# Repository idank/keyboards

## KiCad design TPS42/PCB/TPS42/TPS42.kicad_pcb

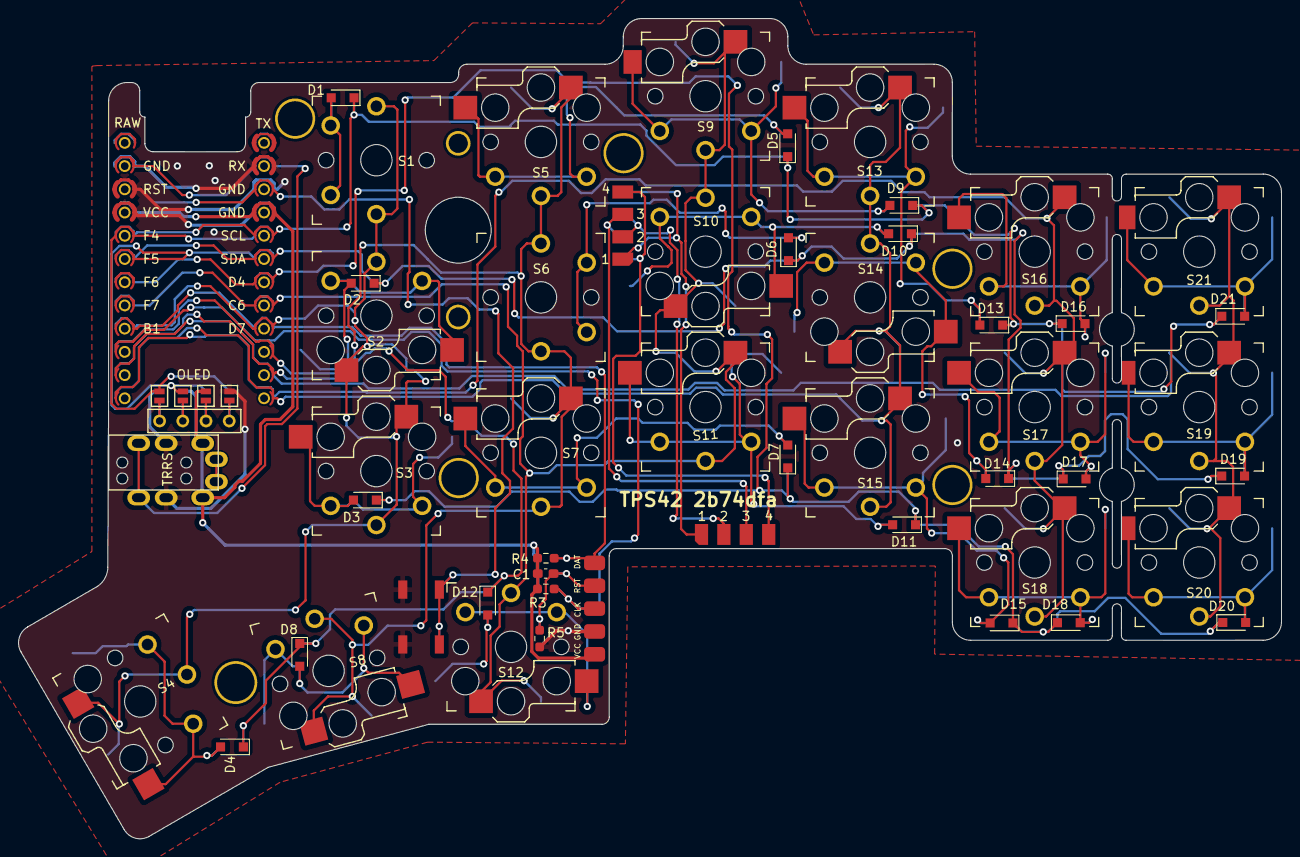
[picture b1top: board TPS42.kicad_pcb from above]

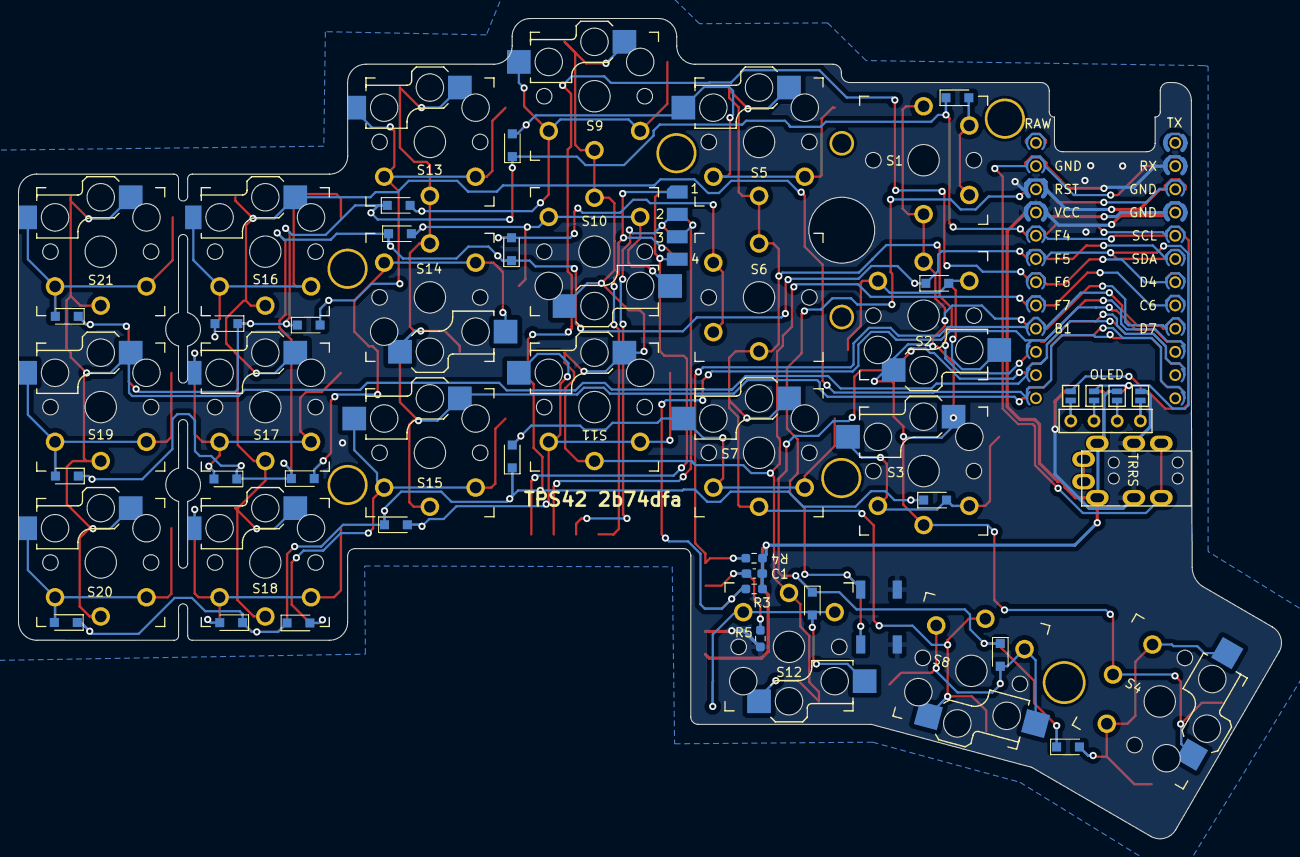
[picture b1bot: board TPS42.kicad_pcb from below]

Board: 2 copper layers, 138.1 x 89.7 mm, 71 parts (7 on the bottom side), 48 nets.

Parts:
C1: 2.2uF; C_0603_1608Metric_Pad1.08x0.95mm_HandSolder_Reversable
D1, D2, D3, D4, D5, D6, D7, D8, D9, D10, D11, D12, D13, D14, D15, D16, D17, D18, D19, D20, D21: D_Small; D_SOD-323_HandSoldering_Reversable
J1: MJ-4PP-9
J2: OLED
J3, J9: TP Sensor Module; TPSensorModule_Connector
J4: TP Module; TPSensorModule_Connector
J7: TrackPoint; TPModule
JP1, JP2, JP3, JP4, JP5, JP6, JP7, JP8: Jumper
R3, R4: 4.7kΩ; R_0603_1608Metric_Pad0.98x0.95mm_HandSolder_Reversable
R5: 100kΩ; R_0603_1608Metric_Pad0.98x0.95mm_HandSolder_Reversable
S1, S6: Switch; SW_PG1350_reversible
S2, S3, S5, S7, S8, S9, S10, S11, S12, S13, S14, S15, S16, S17, S18, S19, S20, S21: Switch; Kailh_socket_PG1350_optional_reversible.kicad_mod
S4: Switch; Kailh_socket_PG1350_125_optional_reversible.kicad_mod
SW2, SW3: Reset; SMD-SW-4_5.1x5.1x2.5
U1: ProMicro; ProMicro_Flipped_v2_A
U4, U5, U7, U8, U9, U12: Hole; HOLE_M2_TH
U11: Hole; TPSensorModule
U14: ProMicro; ProMicro_Flipped_v2_B

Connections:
COL0: S1.1, S2.1, S3.1, S4.1, U1.16 (B1/15), U14.16 (B1/15)
COL1: S5.1, S6.1, S7.1, S8.1, U1.15 (B3/14), U14.15 (B3/14)
COL2: S9.1, S10.1, S11.1, S12.1, U1.17 (F7/A0), U14.17 (F7/A0)
COL3: S13.1, S14.1, S15.1, U1.13 (B6/10), U14.13 (B6/10)
COL4: S16.1, S17.1, S18.1, U1.12 (9/B5), U14.12 (9/B5)
COL5: S19.1, S20.1, S21.1, U1.11 (8/B4), U14.11 (8/B4)
GND: J1.C, J7.4, JP1.1, JP8.1, R5.2, SW2.1, SW3.1, U1.3 (GND), U1.4 (GND), U1.23 (GND), U14.3 (GND), U14.4 (GND), U14.23 (GND)
unnamed: D1.2 (A), S1.2
unnamed: D2.2 (A), S2.2
unnamed: D3.2 (A), S3.2
unnamed: D4.2 (A), S4.2
unnamed: D5.2 (A), S5.2
unnamed: D6.2 (A), S6.2
unnamed: D7.2 (A), S7.2
unnamed: D8.2 (A), S8.2
unnamed: D9.2 (A), S9.2
unnamed: D10.2 (A), S10.2
unnamed: D11.2 (A), S11.2
unnamed: D12.2 (A), S12.2
unnamed: D13.2 (A), S13.2
unnamed: D14.2 (A), S14.2
unnamed: D15.2 (A), S15.2
unnamed: D16.2 (A), S16.2
unnamed: D17.2 (A), S17.2
unnamed: D18.2 (A), S18.2
unnamed: D19.2 (A), S19.2
unnamed: D20.2 (A), S20.2
unnamed: D21.2 (A), S21.2
unnamed: J2.1, JP4.2, JP8.2
unnamed: J2.2, JP3.2, JP7.2
unnamed: J2.3, JP2.2, JP6.2
unnamed: J2.4, JP1.2, JP5.2
unnamed: J3.1, J4.1, J9.1
unnamed: J3.2, J4.2, J9.2
unnamed: J3.3, J4.3, J9.3
unnamed: J3.4, J4.4, J9.4
unnamed: C1.2, J7.2, R5.1
RESET: SW2.2, SW3.2, U1.22 (RST), U14.22 (RST)
ROW0: D1.1 (K), D5.1 (K), D9.1 (K), D13.1 (K), D16.1 (K), D21.1 (K), U1.20 (F4/A3), U14.20 (F4/A3)
ROW1: D2.1 (K), D6.1 (K), D10.1 (K), D14.1 (K), D17.1 (K), D19.1 (K), U1.19 (F5/A2), U14.19 (F5/A2)
ROW2: D3.1 (K), D7.1 (K), D11.1 (K), D15.1 (K), D18.1 (K), D20.1 (K), U1.18 (F6/A1), U14.18 (F6/A1)
ROW3: D4.1 (K), D8.1 (K), D12.1 (K), U1.14 (B2/16), U14.14 (B2/16)
SCL: JP3.1, JP6.1, U1.6 (3/D0/SCL), U14.6 (3/D0/SCL)
SDA: JP4.1, JP5.1, U1.5 (2/D1/SDA), U14.5 (2/D1/SDA)
SERIAL: J1.B, U1.2 (RX1/D2), U14.2 (RX1/D2)
TP_CLK: J7.3, R3.2, U1.10 (7/E6), U14.10 (7/E6)
TP_DATA: J7.1, R4.2, U1.9 (6/D7), U14.9 (6/D7)
VCC: C1.1, J1.D, J7.5, JP2.1, JP7.1, R3.1, R4.1, U1.21 (VCC), U14.21 (VCC)

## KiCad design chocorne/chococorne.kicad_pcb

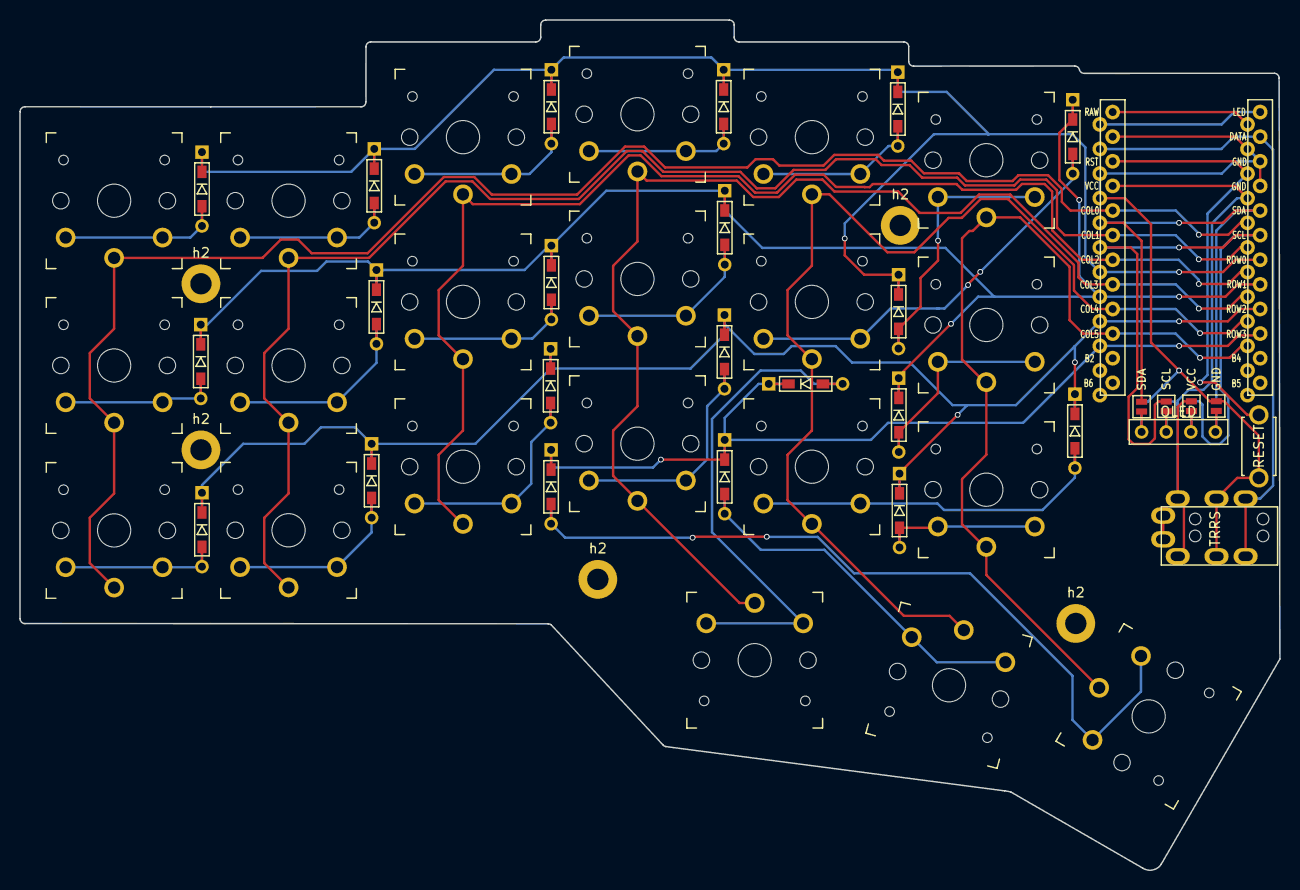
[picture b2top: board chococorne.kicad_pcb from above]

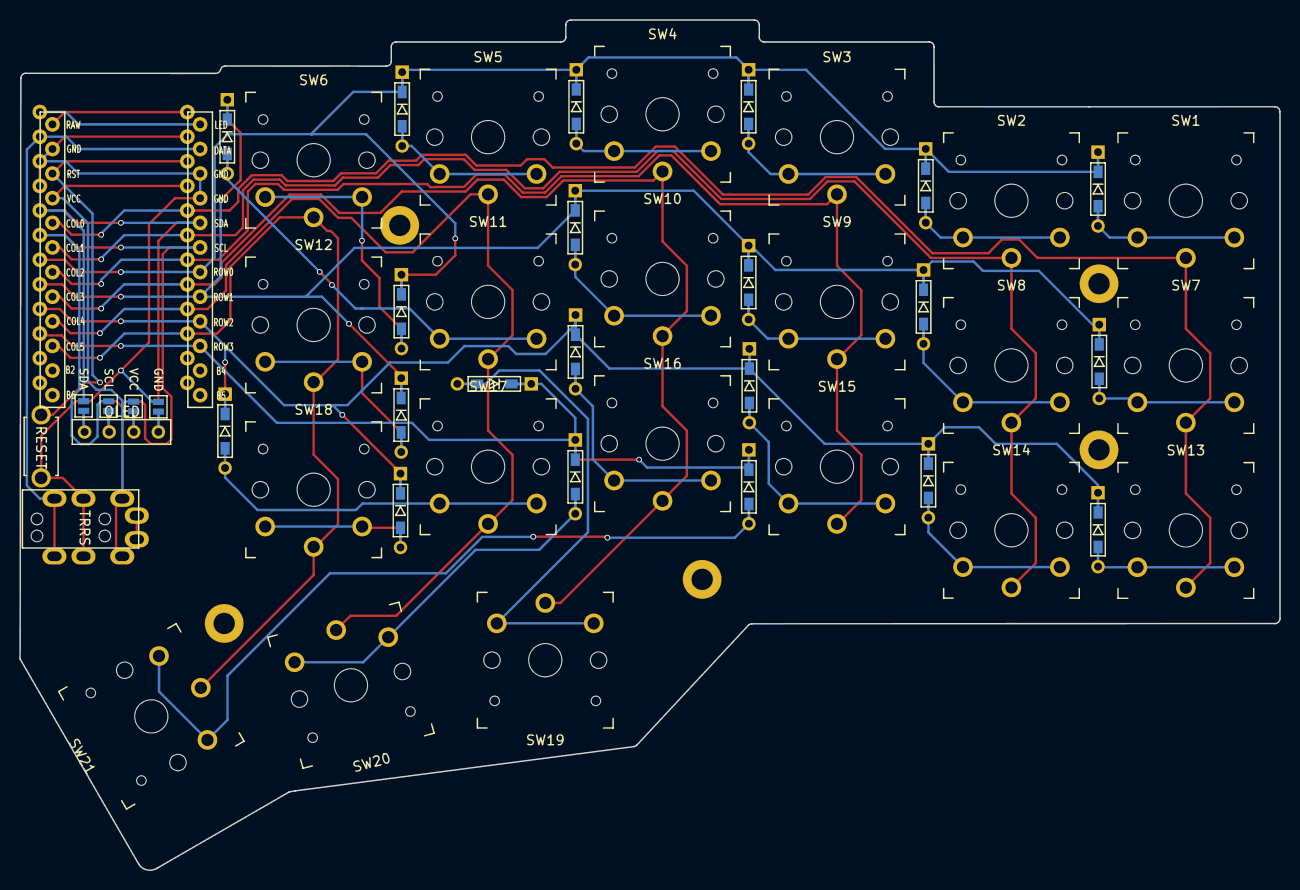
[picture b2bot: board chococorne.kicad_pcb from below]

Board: 2 copper layers, 130.0 x 87.7 mm, 59 parts (4 on the bottom side), 41 nets.

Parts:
D1, D2, D3, D4, D5, D6, D7, D8, D9, D10, D11, D12, D13, D14, D15, D16, D17, D18, D19, D20, D21: D; D3_TH_SMD
J1: MJ-4PP-9
J2: OLED
JP6, JP61: SDA; Jumper
JP62, JP68: GND; Jumper
JP63, JP66: SCL; Jumper
JP64, JP65: VCC; Jumper
RSW1: Val**; ResetSW
SW1, SW2, SW3, SW4, SW5, SW6, SW7, SW8, SW9, SW10, SW11, SW12, SW13, SW14, SW15, SW16, SW17, SW18, SW19, SW20: SW_PUSH; SW_PG1350_reversible_b2
SW21: SW_PUSH; SW_PG1350_15_reversible_b2
U1: ProMicro; ProMicro_v2
h2, h2#2, h2#3, h2#4, h2#5: h2; LEGO_HOLE

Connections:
GND: J1.C, JP62.1, JP68.1, RSW1.1, U1.3, U1.4, U1.23
unnamed: D1.2, SW1.2
unnamed: D2.2, SW2.2
unnamed: D3.2, SW3.2
unnamed: D4.2, SW4.2
unnamed: D5.2, SW5.2
unnamed: D6.2, SW6.2
unnamed: D7.2, SW7.2
unnamed: D8.2, SW8.2
unnamed: D9.2, SW9.2
unnamed: D10.2, SW10.2
unnamed: D11.2, SW11.2
unnamed: D12.2, SW12.2
unnamed: D13.2, SW13.2
unnamed: D14.2, SW14.2
unnamed: D15.2, SW15.2
unnamed: D16.2, SW16.2
unnamed: D17.2, SW17.2
unnamed: D18.2, SW18.2
unnamed: D19.2, SW19.2
unnamed: D20.2, SW20.2
unnamed: D21.2, SW21.2
unnamed: J2.3, JP65.2, JP66.2
unnamed: J2.4, JP6.2, JP68.2
unnamed: J2.2, JP63.2, JP64.2
unnamed: J2.1, JP61.2, JP62.2
SCL: JP63.1, JP66.1, U1.6
SDA: JP6.1, JP61.1, U1.5
VCC: J1.D, JP64.1, JP65.1, U1.21
col0: SW1.1, SW7.1, SW13.1, U1.20
col1: SW2.1, SW8.1, SW14.1, U1.19
col2: SW3.1, SW9.1, SW15.1, U1.18
col3: SW4.1, SW10.1, SW16.1, SW19.1, U1.17
col4: SW5.1, SW11.1, SW17.1, SW20.1, U1.16
col5: SW6.1, SW12.1, SW18.1, SW21.1, U1.15
data: J1.B, U1.2
reset: RSW1.2, U1.22
row0: D1.1, D2.1, D3.1, D4.1, D5.1, D6.1, U1.7
row1: D7.1, D8.1, D9.1, D10.1, D11.1, D12.1, U1.8
row2: D13.1, D14.1, D15.1, D16.1, D17.1, D18.1, U1.9
row3: D19.1, D20.1, D21.1, U1.10
